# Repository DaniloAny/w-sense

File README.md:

## W-SENSE

- the w-sense is a soil moisture sensor that uses a esp32-c3-mini-1 module as its brains.

- currently this project is in heavy work in progress.
- i hope you like it!

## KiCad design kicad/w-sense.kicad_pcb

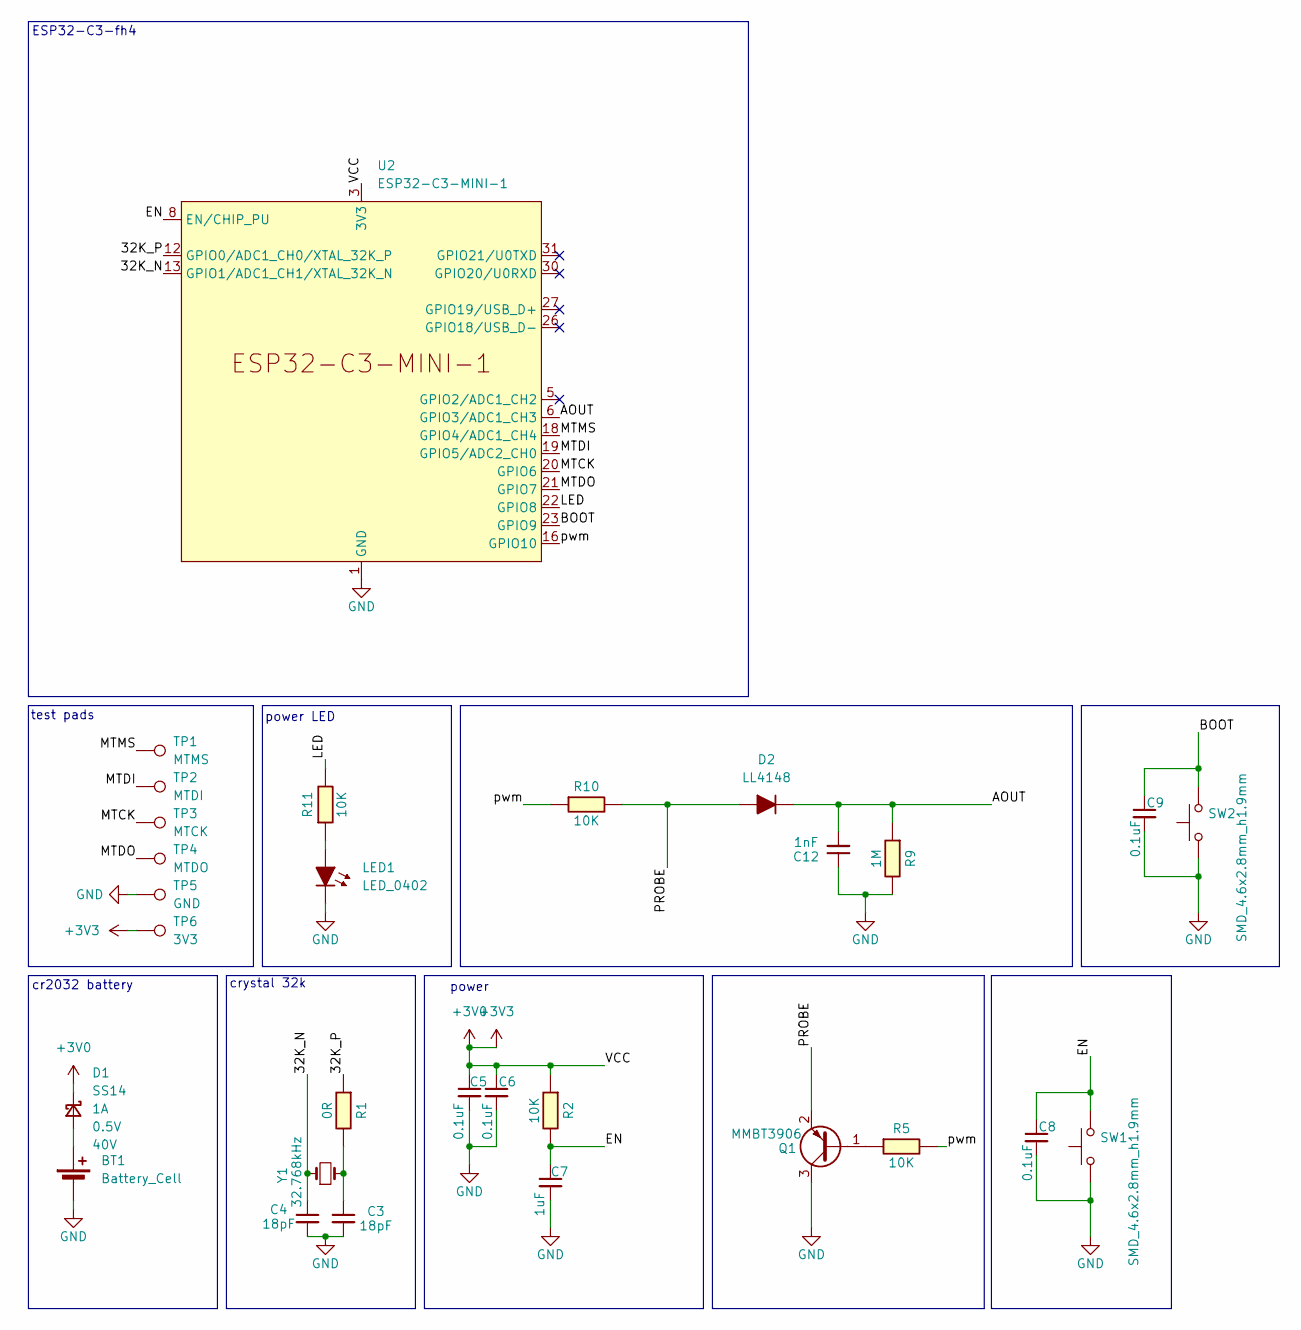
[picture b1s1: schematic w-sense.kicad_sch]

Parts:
BT1: Battery_Cell; BatteryHolder_Keystone_3002_1x2032
C3, C4: 18pF; C_0402_1005Metric; Voltage 50V; Tolerance 5%
C5, C6, C8, C9: 0.1uF; C_0402_1005Metric; Voltage 50V; Tolerance 5%
C7: 1uF; C_0402_1005Metric; Voltage 50V; Tolerance 5%
C12: 1nF; C_0402_1005Metric; Voltage 50V; Tolerance 5%
D1: SS14; D_0603_1608Metric
D2: LL4148; D_MiniMELF
LED1: LED_0402; LED_0402_1005Metric
Q1: MMBT3906; SOT-23
R1: 0R; R_0402_1005Metric
R2, R11: 10K; R_0402_1005Metric
R5, R10: 10K; R_0603
R9: 1M; R_0402_1005Metric
SW1, SW2: SMD_4.6x2.8mm_h1.9mm; Push_SMD_4.6x2.8mm_h1.9mm
TP1: MTMS; TestPoint_Pad_D1.0mm
TP2: MTDI; TestPoint_Pad_D1.0mm
TP3: MTCK; TestPoint_Pad_D1.0mm
TP4: MTDO; TestPoint_Pad_D1.0mm
TP5: GND; TestPoint_Pad_D1.0mm
TP6: 3V3; TestPoint_Pad_D1.0mm
U2: ESP32-C3-MINI-1
Y1: 32.768kHz; Crystal_SMD_3.2x1.5mm

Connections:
+3V0: C5.1, C6.1, D1.1 (K), R2.2, TP6.1 (1_1), U2.3 (3V3)
/32K_N: C4.1, U2.13 (GPIO1/ADC1_CH1/XTAL_32K_N), Y1.1
/32K_P: R1.2, U2.12 (GPIO0/ADC1_CH0/XTAL_32K_P)
/AOUT: C12.2, D2.1 (K), R9.2, U2.6 (GPIO3/ADC1_CH3)
/BOOT: C9.1, SW2.2, U2.23 (GPIO9)
/EN: C7.1, C8.1, R2.1, SW1.2, U2.8 (EN/CHIP_PU)
/LED: R11.1, U2.22 (GPIO8)
/MTCK: TP3.1 (1_1), U2.20 (GPIO6)
/MTDI: TP2.1 (1_1), U2.19 (GPIO5/ADC2_CH0)
/MTDO: TP4.1 (1_1), U2.21 (GPIO7)
/MTMS: TP1.1 (1_1), U2.18 (GPIO4/ADC1_CH4)
/PROBE: D2.2 (A), Q1.2 (E), R10.1
/pwm: R5.1, R10.2, U2.16 (GPIO10)
GND: BT1.2 (-), C3.2, C4.2, C5.2, C6.2, C7.2, C8.2, C9.2, C12.1, LED1.1 (K), Q1.3 (C), R9.1, SW1.1, SW2.1, TP5.1 (1_1), U2.1 (GND), U2.2 (GND), U2.11 (GND), U2.14 (GND), U2.36 (GND), U2.37 (GND), U2.38 (GND), U2.39 (GND), U2.40 (GND), U2.41 (GND), U2.42 (GND), U2.43 (GND), U2.44 (GND), U2.45 (GND), U2.46 (GND), U2.47 (GND), U2.48 (GND), U2.49 (GND), U2.50 (GND), U2.51 (GND), U2.52 (GND), U2.53 (GND)
unnamed: BT1.1 (+), D1.2 (A)
unnamed: C3.1, R1.1, Y1.2
unnamed: LED1.2 (A), R11.2
unnamed: Q1.1 (B), R5.2

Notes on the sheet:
crystal 32k
power
test pads
ESP32-C3-fh4
cr2032 battery
power LED

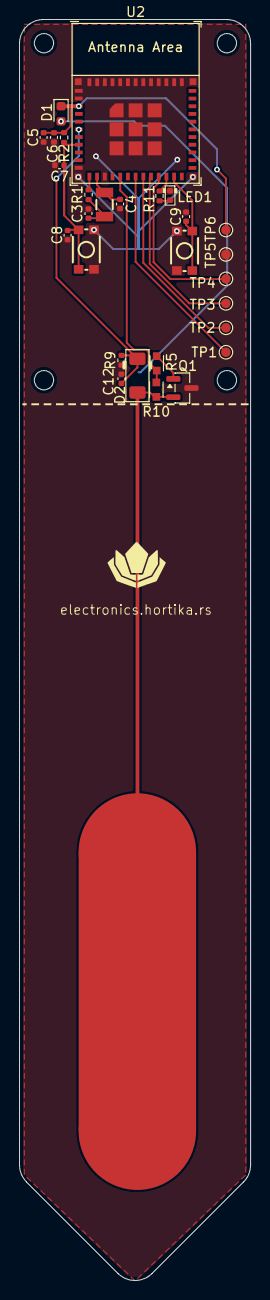
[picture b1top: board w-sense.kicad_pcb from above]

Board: 2 copper layers, 24.0 x 131.0 mm, 29 parts (1 on the bottom side), 18 nets.

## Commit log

2026-06-28 finished pcb and schematic
2026-06-29 minor fixes and added some dimensions to the pcb
